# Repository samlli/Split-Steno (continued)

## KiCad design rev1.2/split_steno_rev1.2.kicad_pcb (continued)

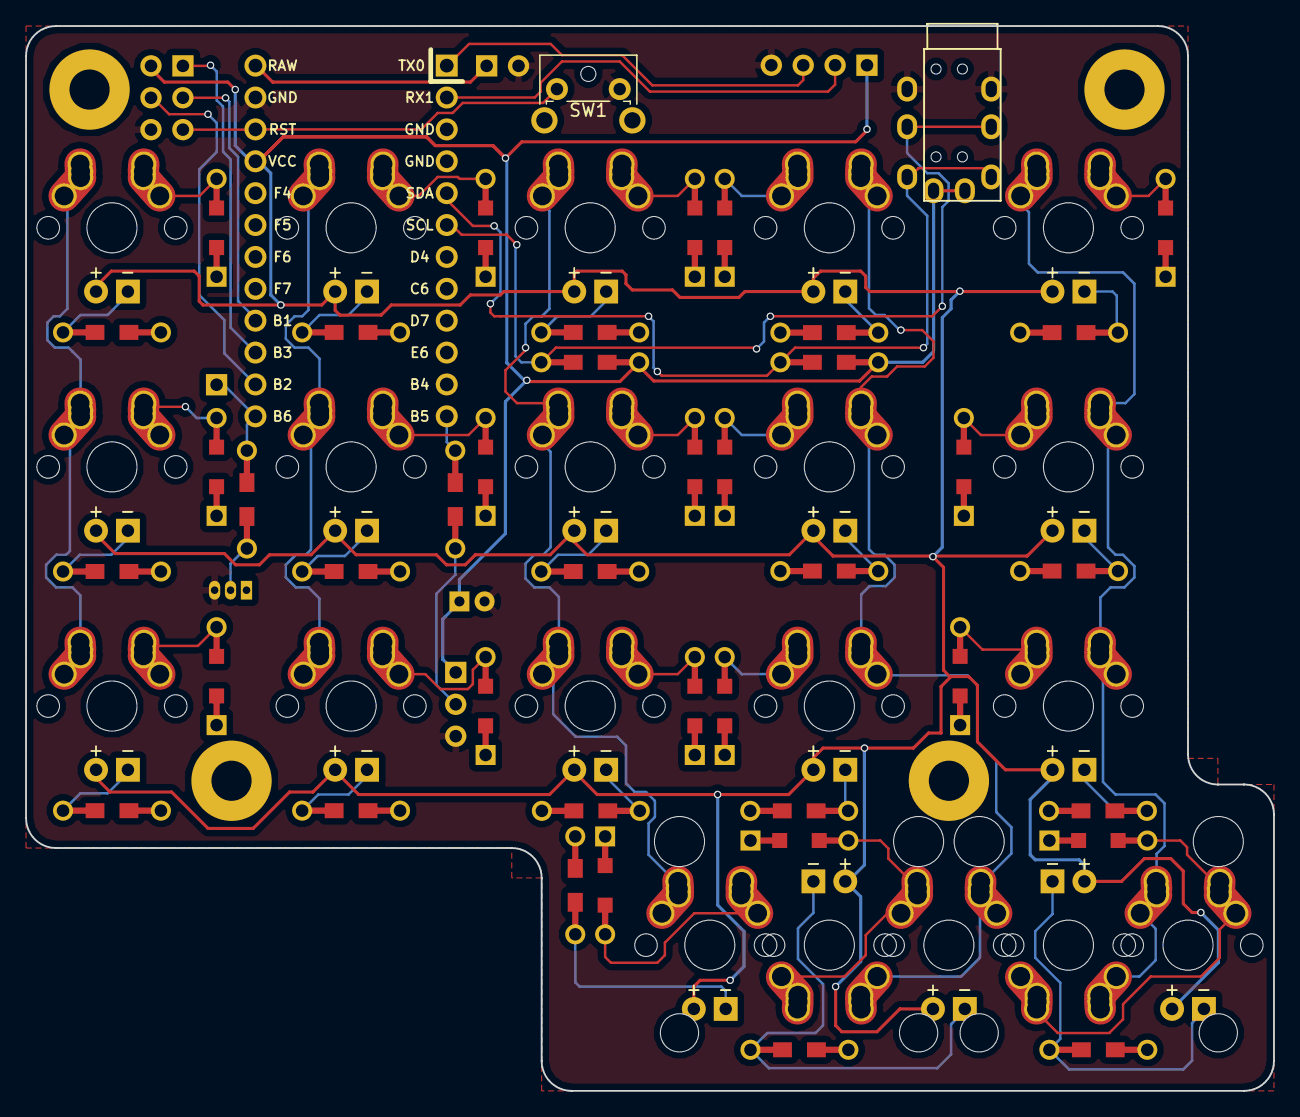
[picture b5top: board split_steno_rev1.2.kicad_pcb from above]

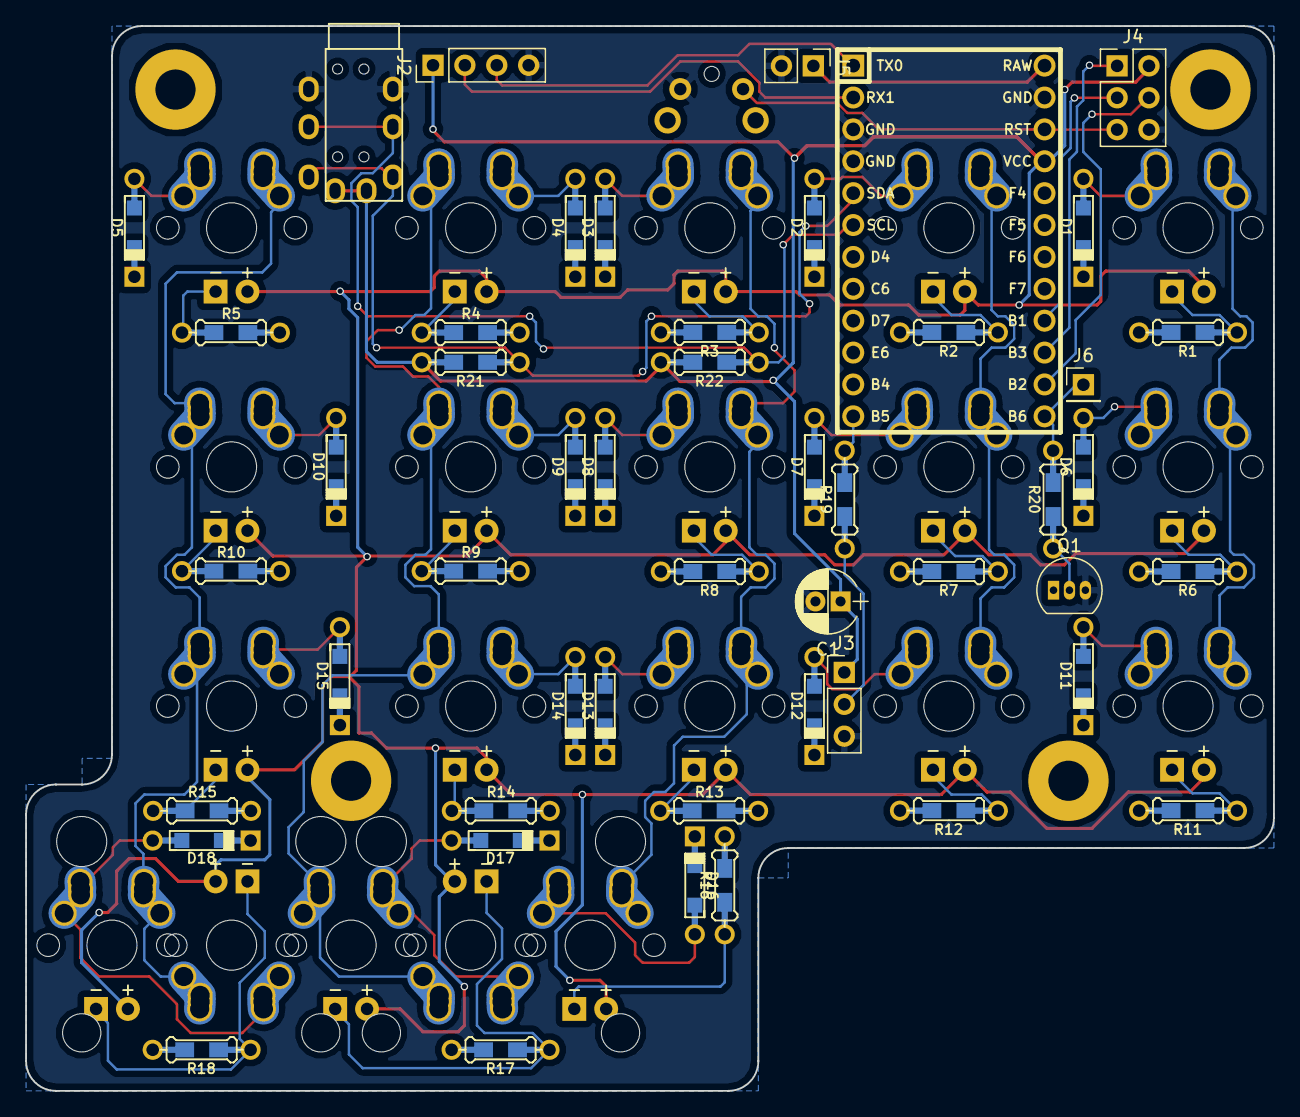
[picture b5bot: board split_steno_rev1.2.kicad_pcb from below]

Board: 2 copper layers, 99.4 x 84.8 mm, 70 parts (49 on the bottom side), 61 nets.

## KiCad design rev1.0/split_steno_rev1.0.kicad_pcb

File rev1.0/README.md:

# rev1.0

**left half**

**right half**

**Features:**

Pro Micro only  
NO mounting holes  
NO breakout for unused pins  
NO silkscreen design aside from name/rev  
First KiCad design - routing etc. not the cleanest

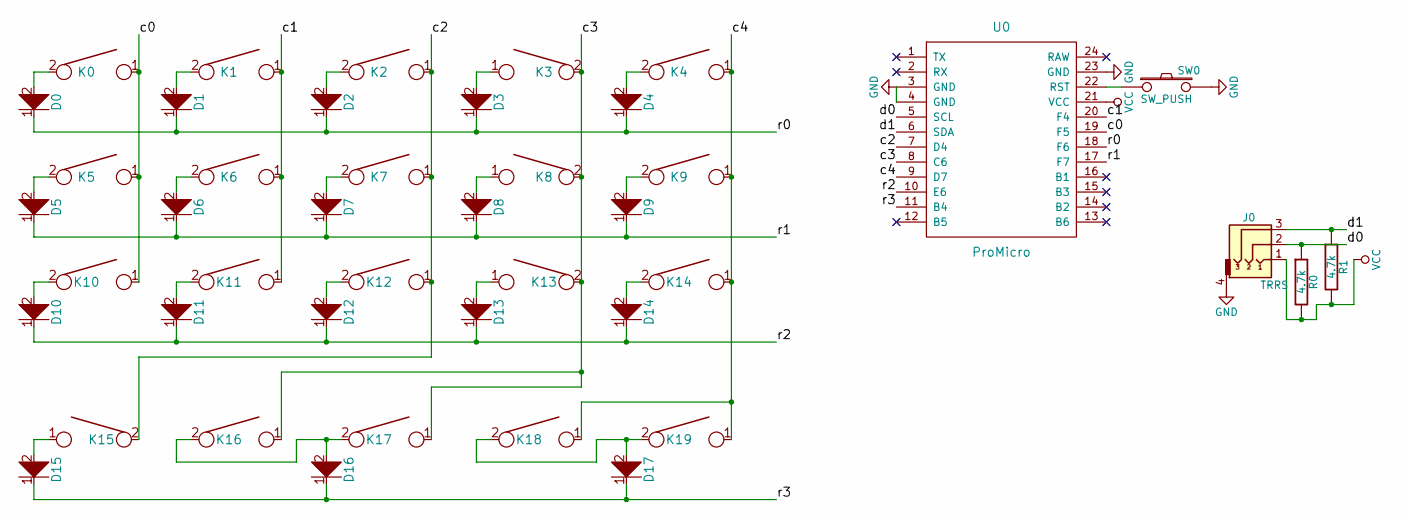
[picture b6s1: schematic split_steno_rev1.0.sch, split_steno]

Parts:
D0, D1, D2, D3, D4, D5, D6, D7, D8, D9, D10, D11, D12, D13, D14, D15, D16, D17: D; Diode-dual
J0: TRRS; TRRS-PJ-320A
K0, K1, K2, K3, K4, K5, K6, K7, K8, K9, K10, K11, K12, K13, K14, K15, K17, K19: KEYSW; Hybrid_PCB_100H_Dual_hole
K16, K18: KEYSW; Hybrid_PCB_200H-dual-nosilk
R0, R1: 4.7k; Resistor-Hybrid
SW0: SW_PUSH; SW_Tactile_SPST_Angled_MJTP1117
U0: ProMicro; ArduinoProMicro

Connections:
/c0: K0.1, K5.1, K10.1, U0.19 (F5)
/c1: K1.1, K6.1, K11.1, U0.20 (F4)
/c2: K2.1, K7.1, K12.1, K15.2, U0.7 (D4)
/c3: K3.2, K8.2, K13.2, K16.1, K17.1, U0.8 (C6)
/c4: K4.1, K9.1, K14.1, K18.1, K19.1, U0.9 (D7)
/d0: J0.2, R0.1, U0.5 (SCL)
/d1: J0.3, R1.1, U0.6 (SDA)
/r0: D0.1, D1.1, D2.1, D3.1, D4.1, U0.18 (F6)
/r1: D5.1, D6.1, D7.1, D8.1, D9.1, U0.17 (F7)
/r2: D10.1, D11.1, D12.1, D13.1, D14.1, U0.10 (E6)
/r3: D15.1, D16.1, D17.1, U0.11 (B4)
GND: J0.4, SW0.2, U0.3 (GND), U0.4 (GND), U0.23 (GND)
unnamed: D0.2, K0.2
unnamed: D1.2, K1.2
unnamed: D2.2, K2.2
unnamed: D3.2, K3.1
unnamed: D4.2, K4.2
unnamed: D5.2, K5.2
unnamed: D6.2, K6.2
unnamed: D7.2, K7.2
unnamed: D8.2, K8.1
unnamed: D9.2, K9.2
unnamed: D10.2, K10.2
unnamed: D11.2, K11.2
unnamed: D12.2, K12.2
unnamed: D13.2, K13.1
unnamed: D14.2, K14.2
unnamed: D15.2, K15.1
unnamed: D16.2, K16.2, K17.2
unnamed: D17.2, K18.2, K19.2
unnamed: SW0.1, U0.22 (RST)
VCC: J0.1, R0.2, R1.2, U0.21 (VCC)

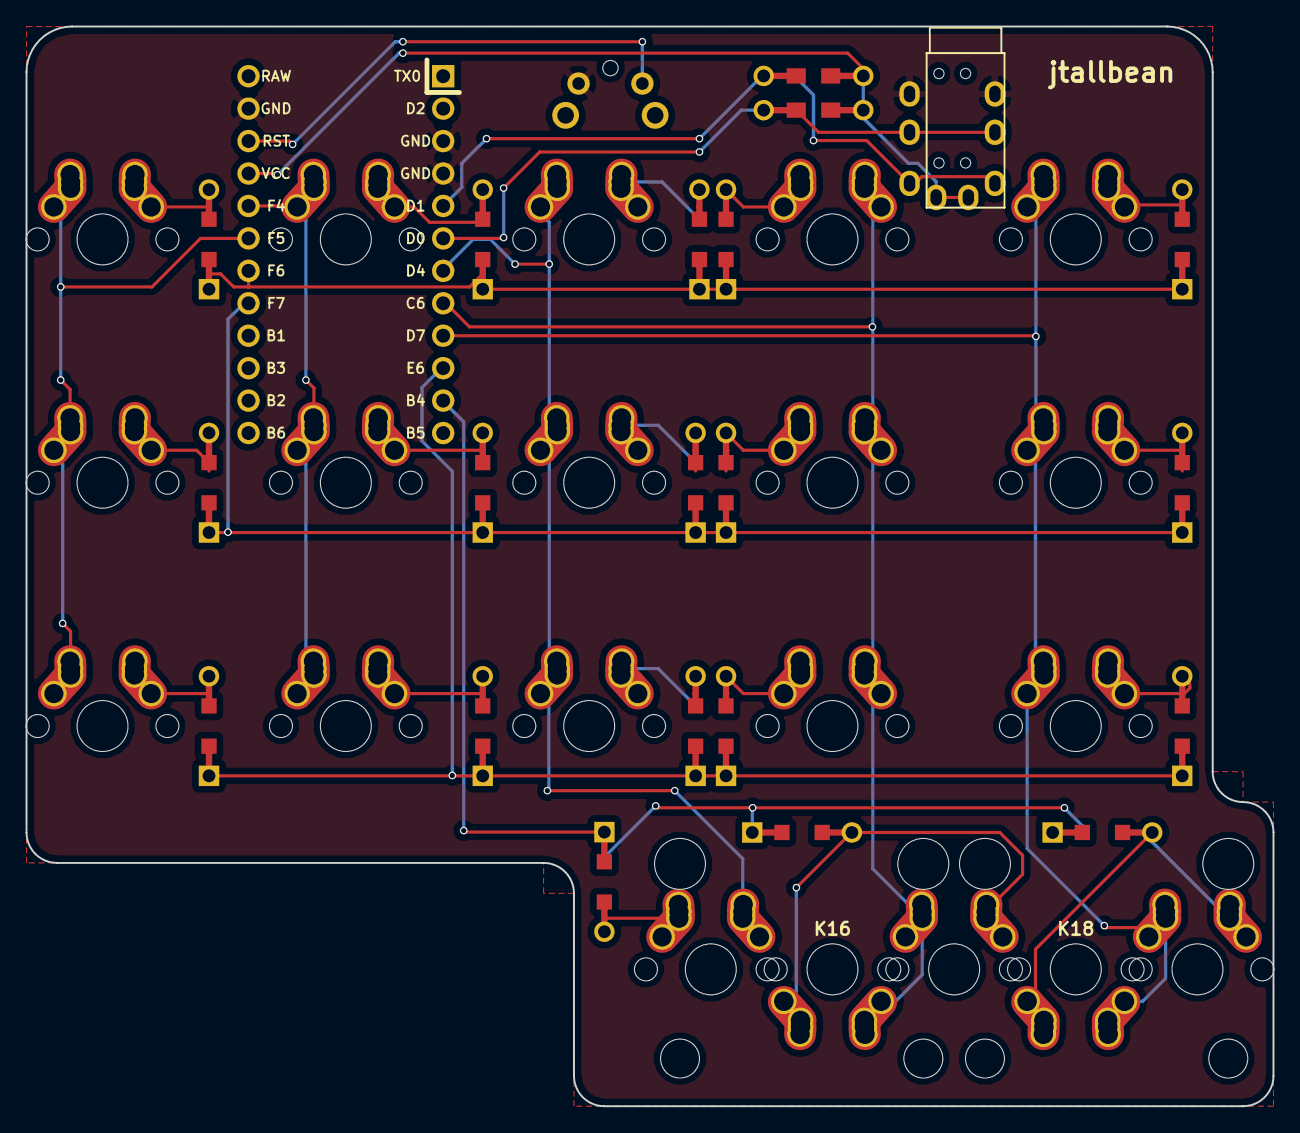
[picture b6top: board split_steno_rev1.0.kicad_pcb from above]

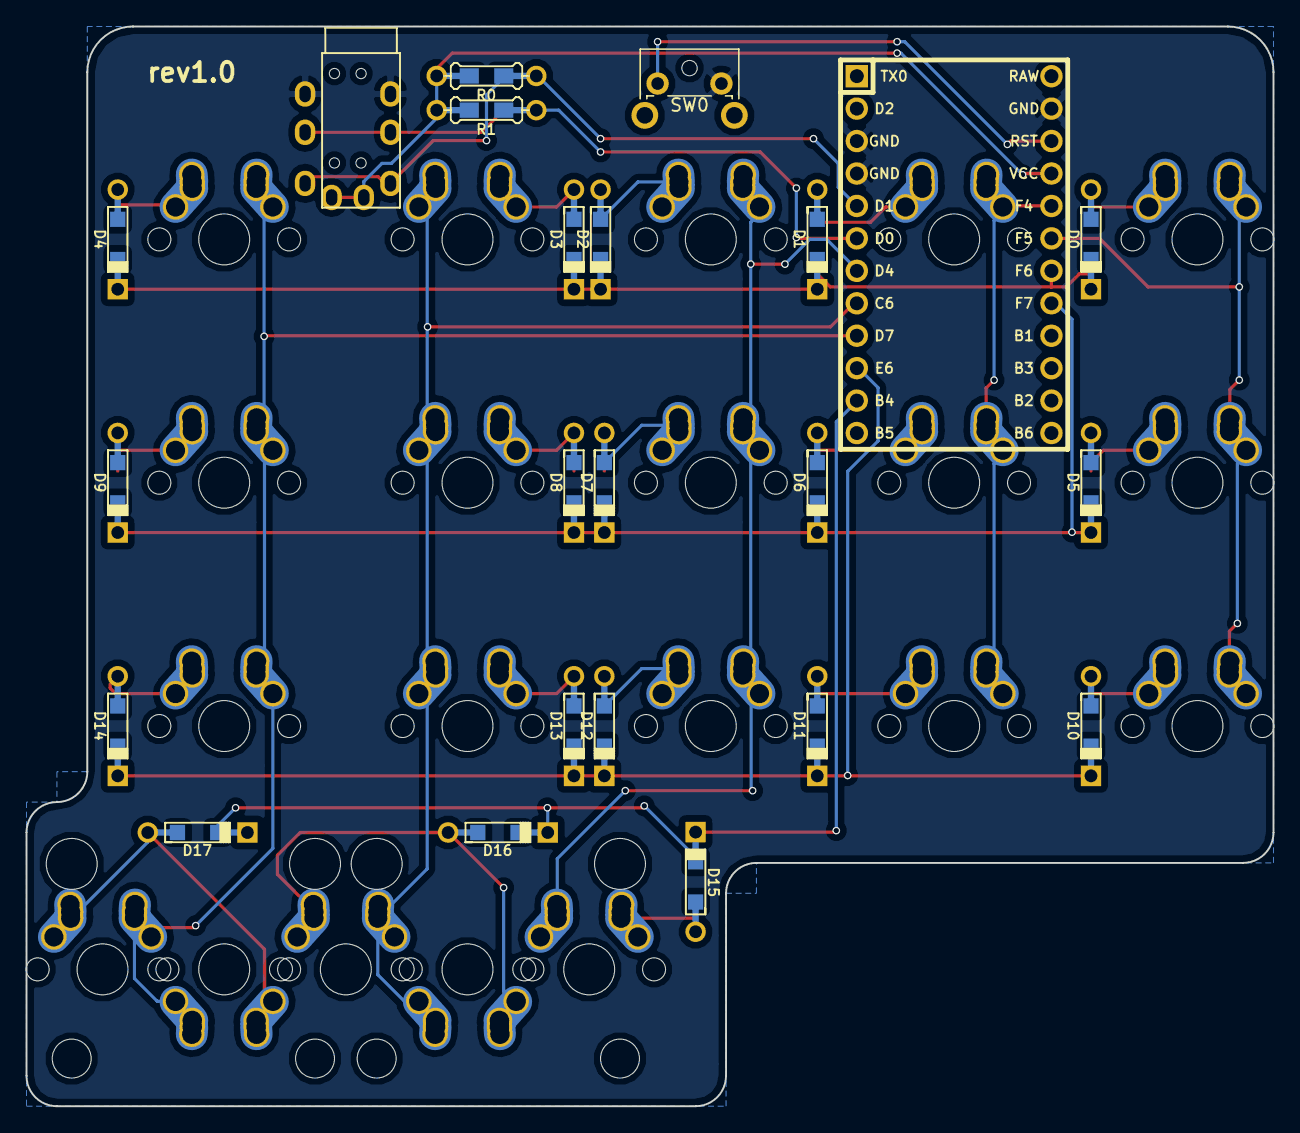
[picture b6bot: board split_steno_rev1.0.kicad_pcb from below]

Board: 2 copper layers, 97.6 x 84.5 mm, 43 parts (22 on the bottom side), 32 nets.

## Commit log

2018-03-01 move into rev1.0
2018-03-01 added ws2812b
2018-03-02 cleaned up schematic
2018-03-07 removed LED backlighting
2018-03-07 laid out, added gnd plane
2018-03-07 removed ws2812b, replaced with breakout
2018-03-08 route vcc
2018-03-08 updated schematic and footprints
2018-03-09 rearranged footprints
2018-03-10 reorganized files
2018-03-11 reorganized schematic library and pro micro footprint
2018-03-11 removed global libraries and moved to local versions
2018-03-11 finished routing traces
2018-03-11 add cool pictures
2018-03-12 begin rev1.1 - I think I know what I'm doing this time...
2018-03-13 schematic using keyboard_parts library
2018-03-13 laid out switch footprints
2018-03-13 laid out led matrix
2018-03-14 laid out mounting holes
2018-03-14 routed non-switch traces
2018-03-15 led/switch routing unfinished - pausing here
    will pause for now - will focus on clean routing and breakouts without leds
2018-03-15 removed led from rev1.1, moved to rev1.2
2018-03-15 finished routing, added silkscreen
2018-03-16 generated gerbers and library managed
2018-03-16 one last thing
2018-03-19 begin rev2.0
2018-03-22 switch and underglow matrix
2018-03-26 some updates
2018-03-27 switch to diodeless matrix, usb otg
2018-03-28 things
2018-03-30 did footprint associations
2018-04-01 begin pcb file
2018-04-05 split 2.0 into 2.1
2018-04-05 reduced components, laid out pcb
2018-04-06 laid out pcb
2018-04-07 added 2 more ws2812b
2018-04-07 finished mounting hole placement
2018-04-08 updated some footprints
2018-04-15 redid edge cuts tighter to switches
2018-04-16 begin working on plate design (cherry+alps with cherry stabilizers)
2018-04-18 removed lipo charging circuit
2018-04-24 reorganized pins, removed NO USB jumper
2018-04-25 laid out components
2018-04-26 routed USB, left side switches
2018-04-27 nrf and usb on both sides of board, rerouted
2018-04-28 rerouted left half
2018-04-28 matched differential pair lengths
2018-04-30 switched from micro to mini b
2018-04-30 added schematic pdf
2018-05-09 added mini usb and tag connect to both sides
2018-05-09 filled in back gnd plane
2018-05-09 added keepout under nrf module
2018-05-11 added universal cherry and alps specific plates
2018-05-13 flipped incorrect stabilizer direction
2018-05-18 rev3.0 - remove reversible pcb, dedicated left/right hand
2018-05-19 added edge cuts, and mounting holes
2018-05-28 things (i forgot what changed)
2018-06-05 finished routing
2018-06-06 starting right hand side
2018-06-06 flipped x values
2018-06-07 library managed
2018-06-11 filled gnd plane on left
2018-06-12 redid right hand side positions to match left hand
2018-06-13 finished right hand
2018-09-13 added license
